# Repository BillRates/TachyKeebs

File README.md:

# TachyKeebs
Just sharing my keyboard projects.

This project uses kicad symbols compiled by Joe Scotto found in [ScottoKeebs](https://github.com/joe-scotto/scottokeebs) project. 

Check him out he makes awesome hand wired boards and compiled together an awesome symbols library.

If you're looking to use these PCBs, fabricate them out on PCBWay and choose: leaded HASL + global direct shipping for the cheapest boards.

Oh and no commercial or privatized selling under any circumstance!!

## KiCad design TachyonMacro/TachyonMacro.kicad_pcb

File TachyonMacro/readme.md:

# Warning

The firmware for the pro micro uses the pro micro ATmega32U4 

If you are using a pro micro with a rp2040, please write your own firmware

:)

Also if you plan to fabricate this board please use JLCPCB.

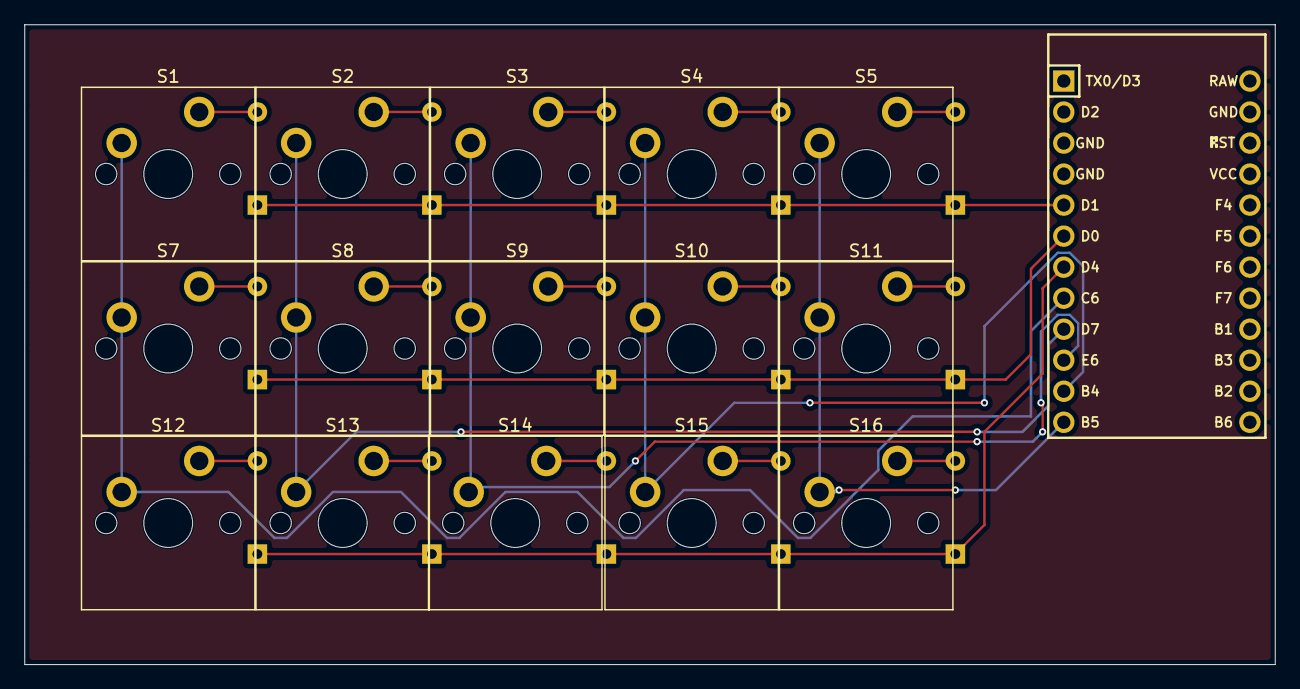
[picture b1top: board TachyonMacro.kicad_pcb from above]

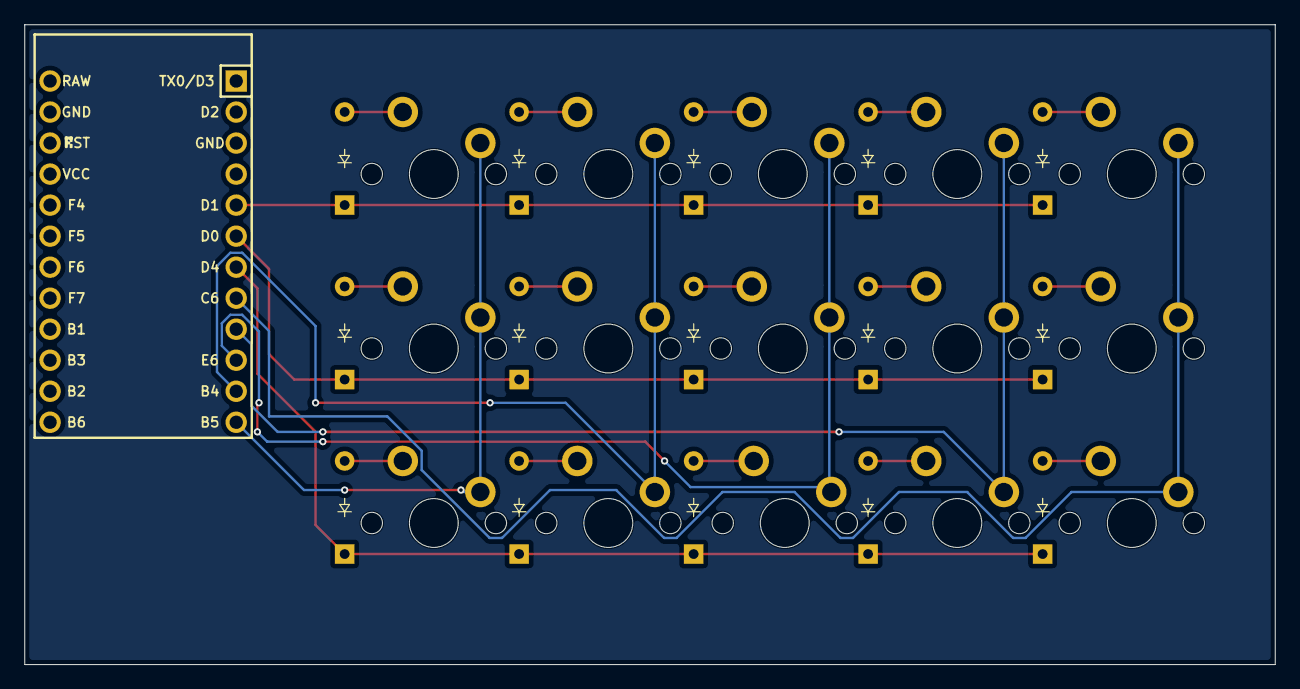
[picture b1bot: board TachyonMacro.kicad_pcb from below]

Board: 2 copper layers, 102.4 x 52.4 mm, 31 parts (15 on the bottom side), 23 nets.

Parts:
D2, D3, D4, D5, D6, D7, D8, D9, D10, D11, D12, D13, D14, D15, D16: Diode_DO-35
S1, S2, S3, S4, S5, S7, S8, S9, S10, S11, S12, S13, S14, S15, S16: MX_PCB_1.00u
U1: Arduino_Pro_Micro

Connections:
Column 0: S1.1, S7.1, S12.1, U1.8 (5/PC6)
Column 1: S2.1, S8.1, S13.1, U1.9 (6/PD7)
Column 2: S3.1, S9.1, S14.1, U1.10 (7/PE6)
Column 3: S4.1, S10.1, S15.1, U1.11 (8/PB4)
Column 4: S5.1, S11.1, S16.1, U1.12 (9/PB5)
unnamed: D2.2 (A), S1.2
unnamed: D3.2 (A), S2.2
unnamed: D4.2 (A), S3.2
unnamed: D5.2 (A), S4.2
unnamed: D6.2 (A), S5.2
unnamed: D7.2 (A), S7.2
unnamed: D8.2 (A), S8.2
unnamed: D9.2 (A), S9.2
unnamed: D10.2 (A), S10.2
unnamed: D11.2 (A), S11.2
unnamed: D12.2 (A), S12.2
unnamed: D13.2 (A), S13.2
unnamed: D14.2 (A), S14.2
unnamed: D15.2 (A), S15.2
unnamed: D16.2 (A), S16.2
Row 0: D2.1 (K), D3.1 (K), D4.1 (K), D5.1 (K), D6.1 (K), U1.5 (2/PD1)
Row 1: D7.1 (K), D8.1 (K), D9.1 (K), D10.1 (K), D11.1 (K), U1.6 (3/PD0)
Row 2: D12.1 (K), D13.1 (K), D14.1 (K), D15.1 (K), D16.1 (K), U1.7 (4/PD4)

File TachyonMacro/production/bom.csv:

Designator,Footprint,Quantity,Value,LCSC Part #
"D10, D11, D12, D13, D14, D15, D16, D2, D3, D4, D5, D6, D7, D8, D9",Diode_DO-35,15,~,
"S1, S10, S11, S12, S13, S14, S15, S16, S2, S3, S4, S5, S7, S8, S9",MX_PCB_1.00u,15,~,
U1,Arduino_Pro_Micro,1,Arduino_Pro_Micro,
